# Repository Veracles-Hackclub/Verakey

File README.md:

# Verakey
A custom Yubikey I'm designing to act as a cool keychain for my backpack! Along with having a keyring for me to mount it to a carabiner, it doesn't have a button, but instead a OLED screen I plan on adding some cute animations to, maybe a frog or something.

It uses the STM32L432KBUx with an ATECC608 for maximum security, and will have the following protocol stack
-FIDO2
-U2F
-HOTP
-PIV

for maximal security. I also added a cool silkscreen.

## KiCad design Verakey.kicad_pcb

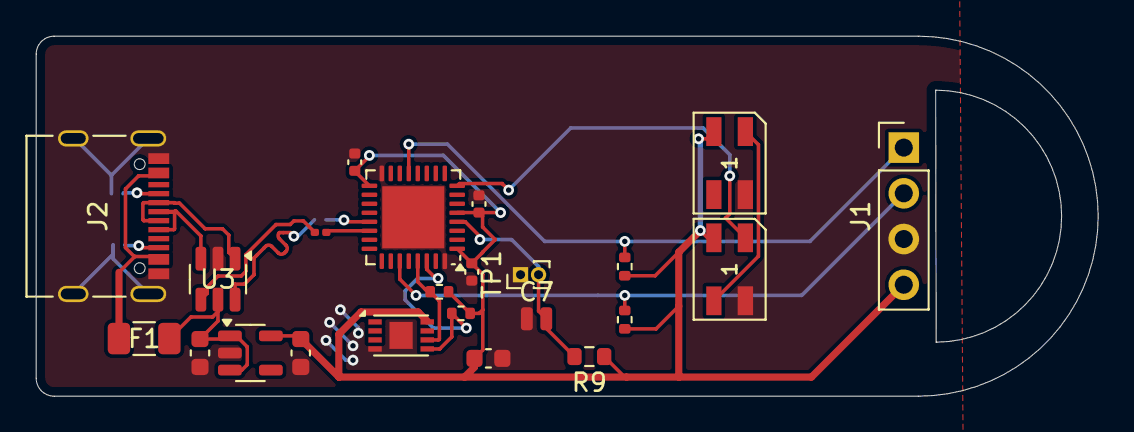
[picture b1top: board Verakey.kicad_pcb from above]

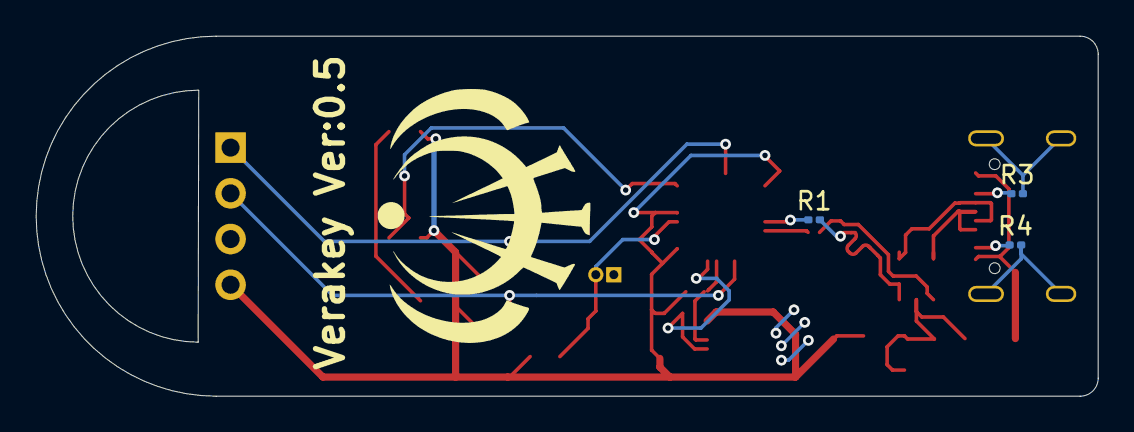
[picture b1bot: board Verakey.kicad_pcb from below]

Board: 2 copper layers, 59.0 x 20.0 mm, 26 parts (3 on the bottom side), 15 nets.

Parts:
C1, C2, C3: 1uF; C_0402_1005Metric
C4: 10uF; C_0603_1608Metric
C5, C6: 1uF; C_0603_1608Metric
C7: 100nF; C_0504_1310Metric
D1, D2: SK6812MINI; LED_SK6812MINI_PLCC4_3.5x3.5mm_P1.75mm
F1: 500mA; Fuse_1206_3216Metric
J1: Conn_01x04_Pin; PinHeader_1x04_P2.54mm_Vertical
J2: USB_C_Receptacle_USB2.0_16P; USB_C_Receptacle_Palconn_UTC16-G
R1, R2: 22; R_0201_0603Metric
R3, R4: 5.1k; R_0201_0603Metric
R5, R6, R7, R8: 4.7k; R_0402_1005Metric
R9: 10k; R_0603_1608Metric
TP1: TestPoint_2Pole; PinHeader_1x02_P1.00mm_Vertical
U1: STM32L432KBUx; QFN-32-1EP_5x5mm_P0.5mm_EP3.45x3.45mm
U2: ATECC608A-MAHDA; DFN-8-1EP_3x2mm_P0.5mm_EP1.3x1.5mm
U3: USBLC6-2SC6; SOT-23-6
U4: TLV75533PDBV; SOT-23-5

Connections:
+3.3V: C1.1, C2.1, C3.1, C4.1, C6.1, D1.4 (VDD), D2.4 (VDD), J1.4, R5.1, R6.1, R7.1, R8.1, R9.1, U1.1 (VDD), U1.5 (VDDA), U1.17 (VDD), U2.8 (VCC), U4.5 (OUT)
D+: J2.A6 (D+), J2.B6 (D+), R2.1, R2.2, U1.22 (PA12), U3.3 (I/O2), U3.4 (I/O2)
D-: J2.A7 (D-), J2.B7 (D-), R1.1, R1.2, U1.21 (PA11), U3.1 (I/O1), U3.6 (I/O1)
GND: C1.2, C2.2, C3.2, C4.2, C5.2, C6.2, C7.1, D1.2 (VSS), D2.2 (VSS), J1.3, J2.A1 (GND), J2.A12 (GND), J2.B1 (GND), J2.B12 (GND), J2.S1 (SHIELD), R3.2, R4.2, TP1.1, U1.16 (VSS), U1.32 (VSS), U1.33 (VSS), U2.4 (GND), U2.9 (EP), U3.2 (GND), U4.2 (GND)
unnamed: D1.1 (DOUT), D2.3 (DIN)
unnamed: J2.A5 (CC1), R3.1
unnamed: J2.B5 (CC2), R4.1
unnamed: C7.2, R9.2, TP1.2, U1.4 (NRST)
PA7: J1.1, R5.2, U1.13 (PA7)
PA8: D1.3 (DIN), U1.8 (PA2)
PB4: J1.2, R6.2, U1.27 (PB4)
PB6: R8.2, U1.29 (PB6), U2.6 (SCL)
PB7: R7.2, U1.30 (PB7), U2.5 (SDA)
VBUS: C5.1, F1.2, U3.5 (VBUS), U4.1 (IN), U4.3 (EN)
VCC: F1.1, J2.A4 (VBUS), J2.A9 (VBUS), J2.B4 (VBUS), J2.B9 (VBUS)

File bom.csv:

reference,qty,value,dnp,exclude from bom,exclude from board,footprint,datasheet,aliexpress price usd,aliexpress total
"C1,C2,C3",3,1uF,,,,"Capacitor_SMD:C_0402_1005Metric",,0.05,0.15
C4,1,10uF,,,,"Capacitor_SMD:C_0603_1608Metric",,0.08,0.08
"C5,C6",2,1uF,,,,"Capacitor_SMD:C_0603_1608Metric",~,0.05,0.10
C7,1,100nF,,,,"Capacitor_SMD:C_0504_1310Metric",,0.05,0.05
"D1,D2",2,SK6812MINI,,,,"LED_SMD:LED_SK6812MINI_PLCC4_3.5x3.5mm_P1.75mm",https://cdn-shop.adafruit.com/product-files/2686/SK6812MINI_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,0.25,0.50
F1,1,500mA,,,,"Fuse:Fuse_1206_3216Metric",~,0.15,0.15
J1,1,Conn_01x04_Pin,,,,"Connector_PinHeader_2.54mm:PinHeader_1x04_P2.54mm_Vertical",~,0.12,0.12
J2,1,USB_C_Receptacle_USB2.0_16P,,,,"Connector_USB:USB_C_Receptacle_Palconn_UTC16-G",https://www.usb.org/sites/default/files/documents/usb_type-c.zip,0.45,0.45
"R1,R2",2,22,,,,"Resistor_SMD:R_0201_0603Metric",~,0.03,0.06
"R3,R4",2,5.1k,,,,"Resistor_SMD:R_0201_0603Metric",~,0.03,0.06
"R5,R6,R7,R8",4,4.7k,,,,"Resistor_SMD:R_0402_1005Metric",~,0.03,0.12
R9,1,10k,,,,"Resistor_SMD:R_0603_1608Metric",~,0.03,0.03
TP1,1,TestPoint_2Pole,,,,"Connector_PinHeader_1.00mm:PinHeader_1x02_P1.00mm_Vertical",~,0.10,0.10
U1,1,STM32L432KBUx,,,,"Package_DFN_QFN:QFN-32-1EP_5x5mm_P0.5mm_EP3.45x3.45mm",https://www.st.com/resource/en/datasheet/stm32l432kb.pdf,3.50,3.50
U2,1,ATECC608A-MAHDA,,,,"Package_DFN_QFN:DFN-8-1EP_3x2mm_P0.5mm_EP1.3x1.5mm",http://ww1.microchip.com/downloads/en/DeviceDoc/ATECC608A-Cr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,0.85,0.85
U3,1,USBLC6-2SC6,,,,"Package_TO_SOT_SMD:SOT-23-6",https://www.st.com/resource/en/datasheet/usblc6-2.pdf,0.18,0.18
U4,1,TLV75533PDBV,,,,"Package_TO_SOT_SMD:SOT-23-5",http://www.ti.com/lit/ds/symlink/tlv755p.pdf,0.35,0.35
,,,,,,,,TOTAL,6.85

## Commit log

2025-10-05 Rename BOM.csv to bom.csv
2025-10-11 First release
